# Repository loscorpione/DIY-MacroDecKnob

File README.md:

# MacroDecKnob
MacroDecKnob32 è un progetto di un Deck a 12 tasti con un Encoder magnetico

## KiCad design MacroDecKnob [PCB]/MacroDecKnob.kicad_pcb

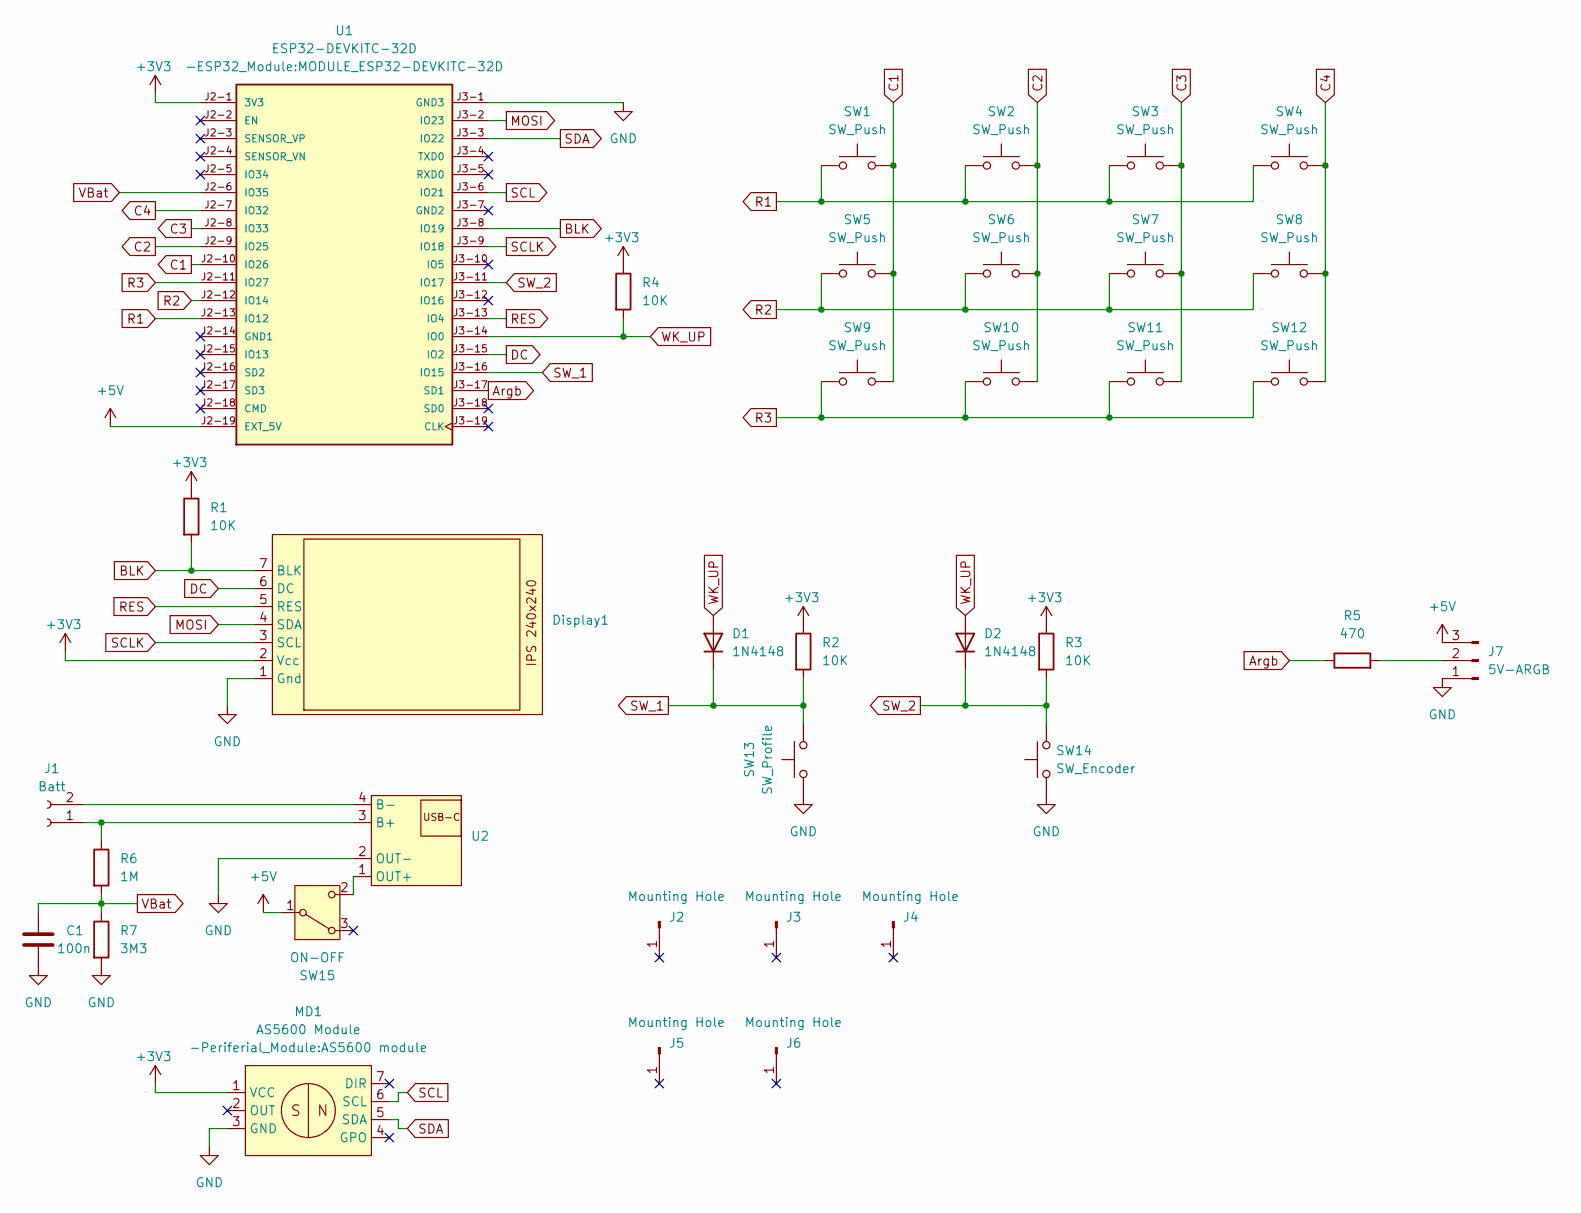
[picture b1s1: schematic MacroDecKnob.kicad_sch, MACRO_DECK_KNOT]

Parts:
C1: 100n; C_Rect_L7.2mm_W2.5mm_P5.00mm_FKS2_FKP2_MKS2_MKP2
D1, D2: 1N4148; D_DO-35_SOD27_P7.62mm_Horizontal
Display1: DISPLAY_TFT_ST7789_1.54
J1: Batt; JST_XH_S2B-XH-A_1x02_P2.50mm_Horizontal
J2, J3, J4, J5, J6: Mounting Hole; MountingHole_3.2mm_M3_DIN965_Pad
J7: 5V-ARGB; PinHeader_1x03_P2.54mm_Vertical
MD1: AS5600 Module; AS5600 module
R1, R2, R3, R4: 10K; R_Axial_DIN0207_L6.3mm_D2.5mm_P7.62mm_Horizontal
R5: 470; R_Axial_DIN0207_L6.3mm_D2.5mm_P7.62mm_Horizontal
R6: 1M; R_Axial_DIN0207_L6.3mm_D2.5mm_P7.62mm_Horizontal
R7: 3M3; R_Axial_DIN0207_L6.3mm_D2.5mm_P7.62mm_Horizontal
SW1, SW2, SW3, SW4, SW5, SW6, SW7, SW8, SW9, SW10, SW11, SW12: SW_Push; SW_Cherry_MX_1.00u_Plate
SW13: SW_Profile; SW_Cherry_MX_1.00u_Plate
SW14: SW_Encoder; SW_Cherry_MX_1.00u_Plate
SW15: ON-OFF; SW_Slide-03_Wuerth-WS-SLTV_10x2.5x6.4_P2.54mm
U1: ESP32-DEVKITC-32D; MODULE_ESP32-DEVKITC-32D; PARTREV V4
U2: LX-LCBST_Batt_Ch_Module

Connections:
+3V3: Display1.2 (Vcc), MD1.1 (VCC), R1.1, R2.1, R3.1, R4.1, U1.J2-1 (3V3)
+5V: J7.3, SW15.1 (B), U1.J2-19 (EXT_5V)
Argb: R5.1, U1.J3-17 (SD1)
BLK: Display1.7 (BLK), R1.2, U1.J3-8 (IO19)
C1: SW1.2, SW5.2, SW9.2, U1.J2-10 (IO26)
C2: SW2.2, SW6.2, SW10.2, U1.J2-9 (IO25)
C3: SW3.2, SW7.2, SW11.2, U1.J2-8 (IO33)
C4: SW4.2, SW8.2, SW12.2, U1.J2-7 (IO32)
DC: Display1.6 (DC), U1.J3-15 (IO2)
GND: C1.2, Display1.1 (Gnd), J7.1, MD1.3 (GND), R7.2, SW13.1, SW14.1, U1.J3-1 (GND3), U2.2 (OUT-)
MOSI: Display1.4 (SDA), U1.J3-2 (IO23)
unnamed: J1.1, R6.1, U2.3 (B+)
unnamed: J1.2, U2.4 (B-)
unnamed: J7.2, R5.2
unnamed: SW15.2 (C), U2.1 (OUT+)
R1: SW1.1, SW2.1, SW3.1, SW4.1, U1.J2-13 (IO12)
R2: SW5.1, SW6.1, SW7.1, SW8.1, U1.J2-12 (IO14)
R3: SW9.1, SW10.1, SW11.1, SW12.1, U1.J2-11 (IO27)
RES: Display1.5 (RES), U1.J3-13 (IO4)
SCL: MD1.6 (SCL), U1.J3-6 (IO21)
SCLK: Display1.3 (SCL), U1.J3-9 (IO18)
SDA: MD1.5 (SDA), U1.J3-3 (IO22)
SW_1: D1.1 (K), R2.2, SW13.2, U1.J3-16 (IO15)
SW_2: D2.1 (K), R3.2, SW14.2, U1.J3-11 (IO17)
VBat: C1.1, R6.2, R7.1, U1.J2-6 (IO35)
WK_UP: D1.2 (A), D2.2 (A), R4.2, U1.J3-14 (IO0)

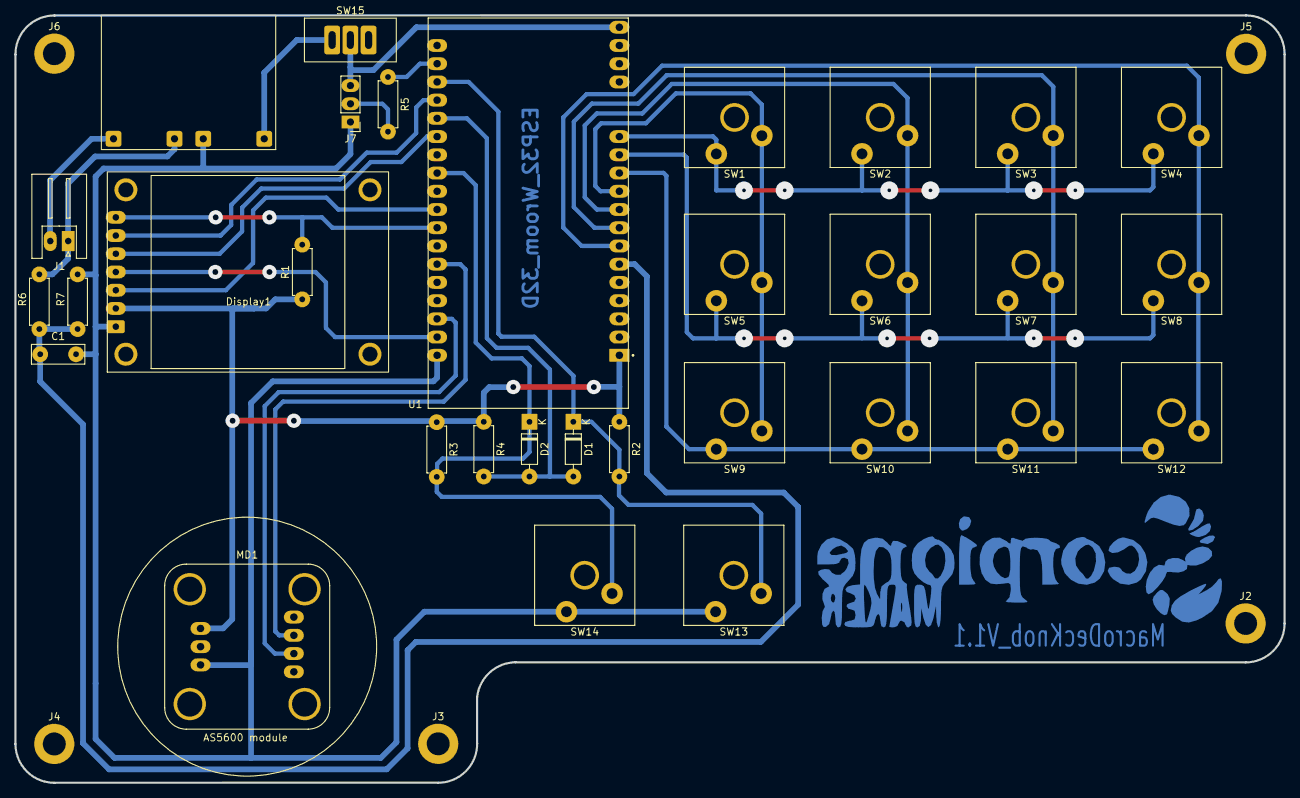
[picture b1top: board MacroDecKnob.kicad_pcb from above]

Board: 2 copper layers, 176.9 x 106.9 mm, 36 parts (0 on the bottom side), 26 nets.

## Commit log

2025-05-07 Initial version
    PlatformIO code,
2025-05-07 Insert Kicad
    Pcb Kicad Files
2025-05-22 Insert Cover
    Prima versione completa della Cover
2025-06-05 upgrade 2"display
    display 320x 240 upgrade
2025-06-07 Upgrade code
    logo iniziale
    logo sleep
    user config
2025-06-20 Mod. Icone e profili
    inserite nuove icone e modificato profili
2025-06-20 Aggiornamento cover e PCB
    Inserito File gerber e file PDF 1:1
    Inserito STL stampabili
2025-06-20 update battery icon on start
